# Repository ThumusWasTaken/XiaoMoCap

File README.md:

Guide to build and code you TOL, tiny open logger IMU sensor:

1- Arduino code folder:
TinyOpenLogger_Code

2- PCB CAD files folder:
KiCad_files

3- 3D print link: 
https://cad.onshape.com/documents/7f3e29c87ee979af035eb522/w/dbec0ba7e6f450b7338eaabc/e/624f816bbdc67f06185ccd3e?renderMode=0&uiState=68eb8f6068579bafa34129be

4- JLC PCB order folder:
JLCorder_withLED

5- Web user interface code folder:
HTMLWebUI

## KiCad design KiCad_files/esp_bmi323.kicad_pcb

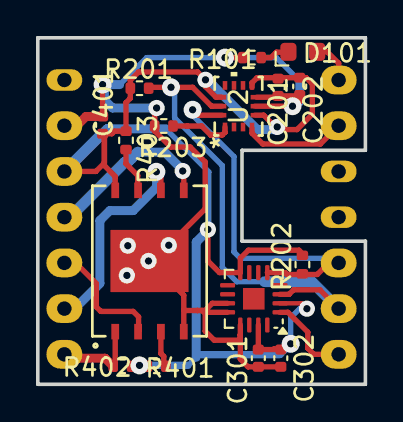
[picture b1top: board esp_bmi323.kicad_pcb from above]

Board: 2 copper layers, 18.2 x 19.2 mm, 17 parts (1 on the bottom side), 14 nets.

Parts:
C201, C202, C301, C302, C401: 100 nF; C_0402_1005Metric
D101: LED; LED_Kingbright_APA1606_1.6x0.6mm_Horizontal
R101: 220; R_0402_1005Metric
R201, R202, R203, R401, R402, R403: 4.7k; R_0402_1005Metric
U1: XIAO ESP32 C3; DIP-14_600_ELL
U2: BMI323; BMI323_BOS
U3: MLX90393; QFN-16-1EP_3x3mm_P0.5mm_EP1.675x1.675mm
U4: W25N01GVZEIG; WSON-8_8X6_WIN

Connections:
+3.3V: C201.1, C202.1, C301.2, C302.2, C401.2, R201.1, R202.1, R401.1, R402.1, R403.1, U1.12 (3V3), U2.5 (VDDIO), U2.8 (VDD), U2.12 (CSB), U3.2 (MS/~CS), U3.8 (VDDIO), U3.15 (VDD), U4.8 (VCC)
GND: C201.2, C202.2, C301.1, C302.1, C401.1, R101.2, R203.2, U1.13 (GND), U2.6 (GNDIO), U2.7 (GND), U3.11 (A1), U3.12 (A0), U3.13 (GND), U4.4 (GND), U4.9 (GND)
GPIO7_MLX90393: U1.7 (GPIO7), U3.1 (INT)
GPIO44_W25N: R402.2, U1.8 (RX), U4.1 (/CS)
MISO_W25N: U1.10 (MISO), U4.2 (DO(IO1))
MOSI_W25N: U1.11 (MOSI), U4.5 (DI(IO0))
unnamed: D101.2 (A), U1.1 (GPIO2)
unnamed: D101.1 (K), R101.1
unnamed: R203.1, U2.1 (SDO)
unnamed: R403.2, U4.7 (/HOLD(IO3))
unnamed: R401.2, U4.3 (/WP(IO2))
SCK_W25N: U1.9 (SCK), U4.6 (CLK)
SCL_BMI323: R201.2, U1.6 (SCL), U2.13 (SCX), U3.3 (SCL/SCLK)
SDA_BMI323: R202.2, U1.5 (SDA), U2.14 (SDX), U3.5 (SDA/MOSI)

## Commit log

2025-07-06 Create JLC order
2025-07-06 Rename esp_bmi323-GERBERS.zip to JLCorder/Gerber_files/esp_bmi323-GERBERS.zip
2025-07-06 Rename esp_bmi323-JLCPCB Assembly Order.xls to JLCorder/esp_bmi323-JLCPCB Assembly Order.xls
2025-07-06 Rename esp_bmi323-pos_numbered.xlsx to JLCorder/CPL/esp_bmi323-pos_numbered.xlsx
2025-07-06 Rename JLC order to JLCorder/Readme
2025-07-06 Rename bmi323_draft.ino to BMI323/bmi323_draft.ino
2025-07-11 Rename mobile_esp32_csv_viewer.html to HTMLwebUI/mobile_esp32_csv_viewer.html
2025-07-11 Create main
2025-07-11 Update and rename main to Readme.txt
    explain which modules it includes
2025-07-11 Rename W25N01GV_progLED/W25N01GV_test_complete.ino to W25N01GV_progLED/W25N01GV_test_complete./W25N01GV_test_complete.ino
2025-07-11 Rename W25N01GV_test_complete.ino to W25N01GV_test_complete.ino
2025-07-15 Add files via upload
    improved UI with CSV auto-save
    future version append the current csv file
2025-07-15 Rename ~esp_bmi323.kicad_pcb.lck to KiCad_files/~esp_bmi323.kicad_pcb.lck
2025-07-15 Rename ~esp_bmi323.kicad_sch.lck to KiCad_files/~esp_bmi323.kicad_sch.lck
2025-09-30 Update BadBlockManager.h
    rectified number of total blocks to correct one
2025-09-30 Update BadBlockManager.cpp
    Change max blocks to 1024 and change uint sizes to correct ones
2025-09-30 Update W25N01GV.h
    chnage all pages declare to uint32
2025-09-30 Update W25N01GV.cpp
    changed max page length and corresponding int declare
2025-09-30 changing max num of pages and corresponding int declares
2025-09-30 Create esp32_csv_GUI_NEW.html
    new GUI format, only captures the data, is compatible with the next release of W25N01GV_test_readwrite.ino
2025-09-30 Update W25N01GV_test_readwrite.ino
    included bmi and mlx data capture codes.
    included wifi and server creation to transfer the data.
    the function handleData is a new version and is compatible with the html GUI: esp32_csv_GUI_NEW or cmd line: curl http://192.168.1.100/data > dump.csv
    reduced interval base value to reach higher data rates (but still far from expected one)
    Added an option to input yes or no to pull the data several times.
2025-09-30 Create W25N01GV_test_readwrite.ino
    copy here so all can be run from the same folder
2025-10-03 new working file with all sensors on, data rate above 100Hz acheivable and interval timing working
2025-10-03 Frequency fixed
2025-10-06 binary + new timestamp
2025-10-06 Update esp32_csv_GUI_NEW.html
    added section to input duration and rate and select which sensors to use in the GUI
2025-10-07 added setting duration and rate from gui
2025-10-09 added all LED and switch settings, corrected the ti,ing interval within the loop, tried to correct some int definitions
2025-10-11 jlc order new files
2025-10-11 reorganising the git
2025-10-12 updated to available sensor on jlc
2025-10-12 modified for bmi270, and added instructions in read me
2025-10-12 Delete JLCorder_withLED/BOM/esp_bmi323_withLED.csv
    bmi323 version
2025-10-12 Delete JLCorder_withLED/CPL/esp_bmi323-pos_numbered_withLED.xlsx
    wrong file with 323
2025-10-12 Update TOL_wifi_to_csv_GUI.html
    use TOL terminology
2025-10-12 TinyOpenLogger_Code add
    Adding code with rest of ESP at end of each loop and LED/switch setting fitting the paper's finite state machine
2025-10-12 Update TinyOpenLogger_Code.ino
    stop wifi at start of script to save battery
2025-10-12 Create LICENSE
2026-04-29 added code for tol2 working
    Using bmi270, bmm150, mlx 90395 and sd card. push button not yet implemented
2026-04-29 Rename imu_logger_sdfat.ino to TOL2_code.ino
2026-04-29 TOL2 code with mlx
